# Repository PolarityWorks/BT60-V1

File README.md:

# BT60 V1

This is the repository of the design files for the Polarity Works [BT60 V1](https://www.polarityworks.com/bt60) containing both schematic and layout files for the soldered and hotswap variants

The files were created in Autodesk Eagle V9.6.2, in the event you do not have a licence for this software we also provide the schematics in PDF format

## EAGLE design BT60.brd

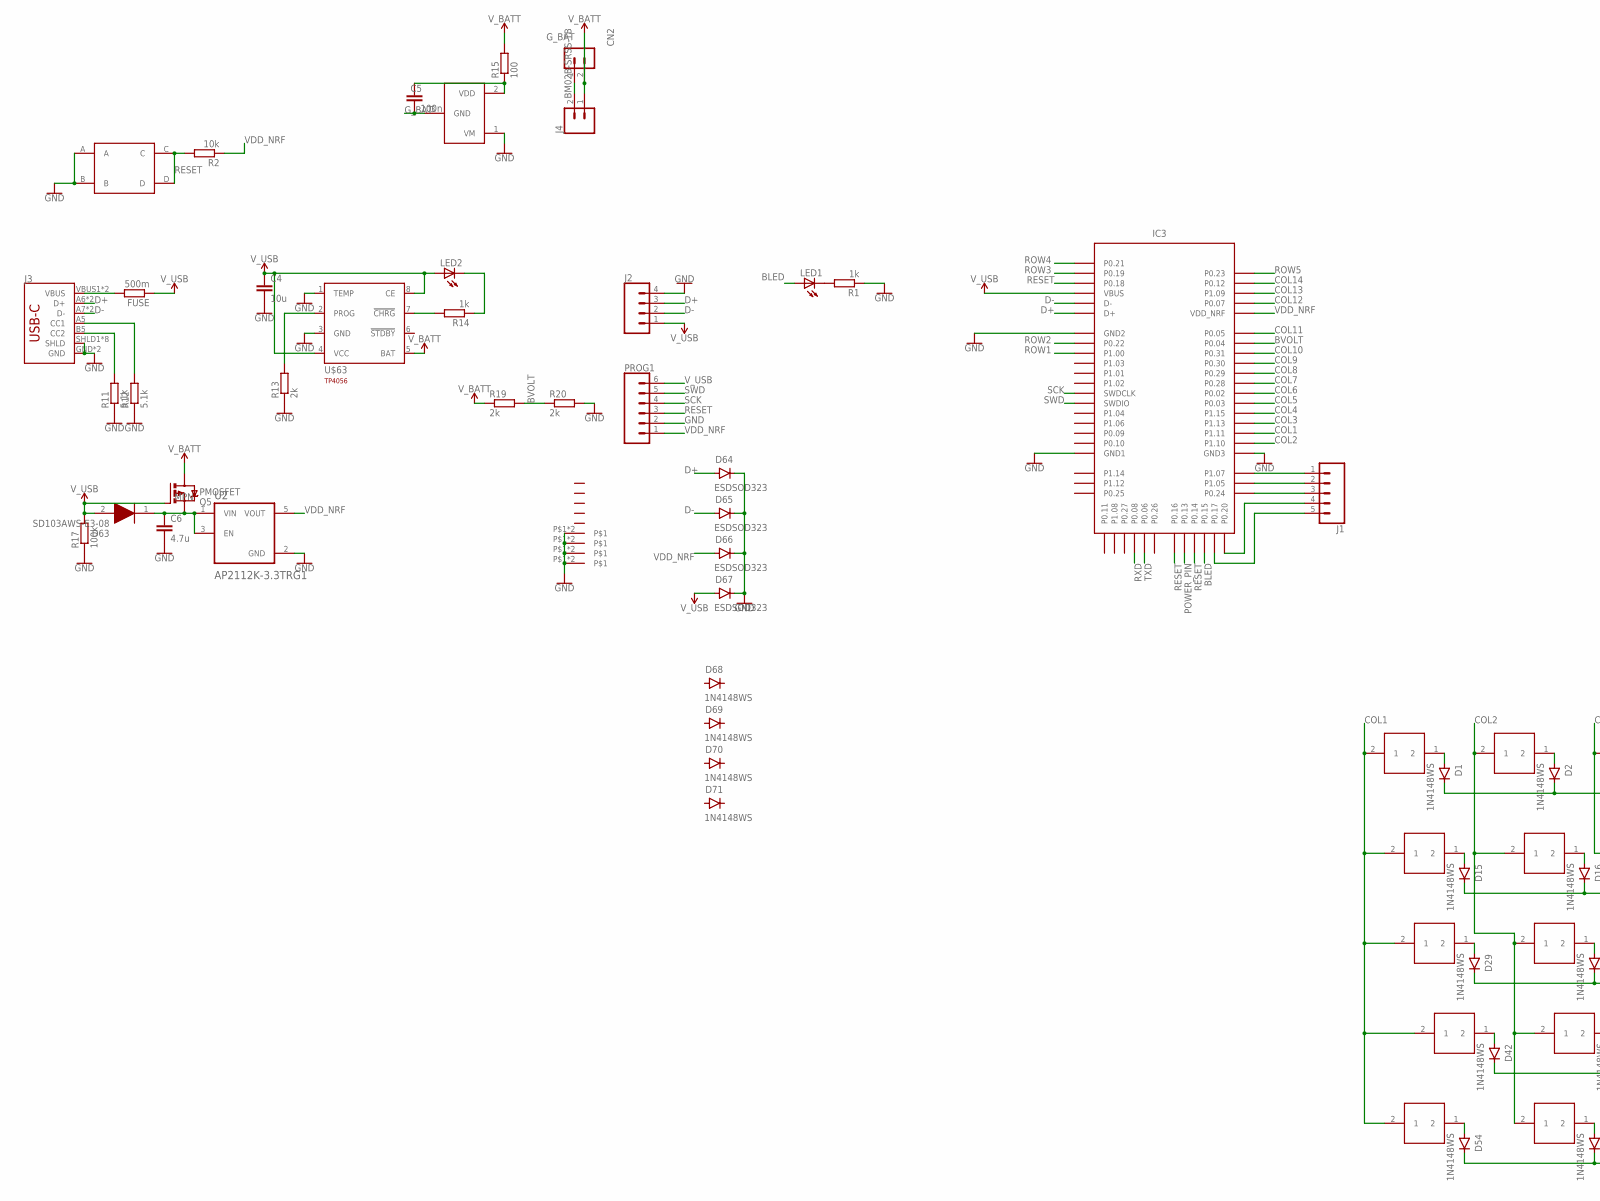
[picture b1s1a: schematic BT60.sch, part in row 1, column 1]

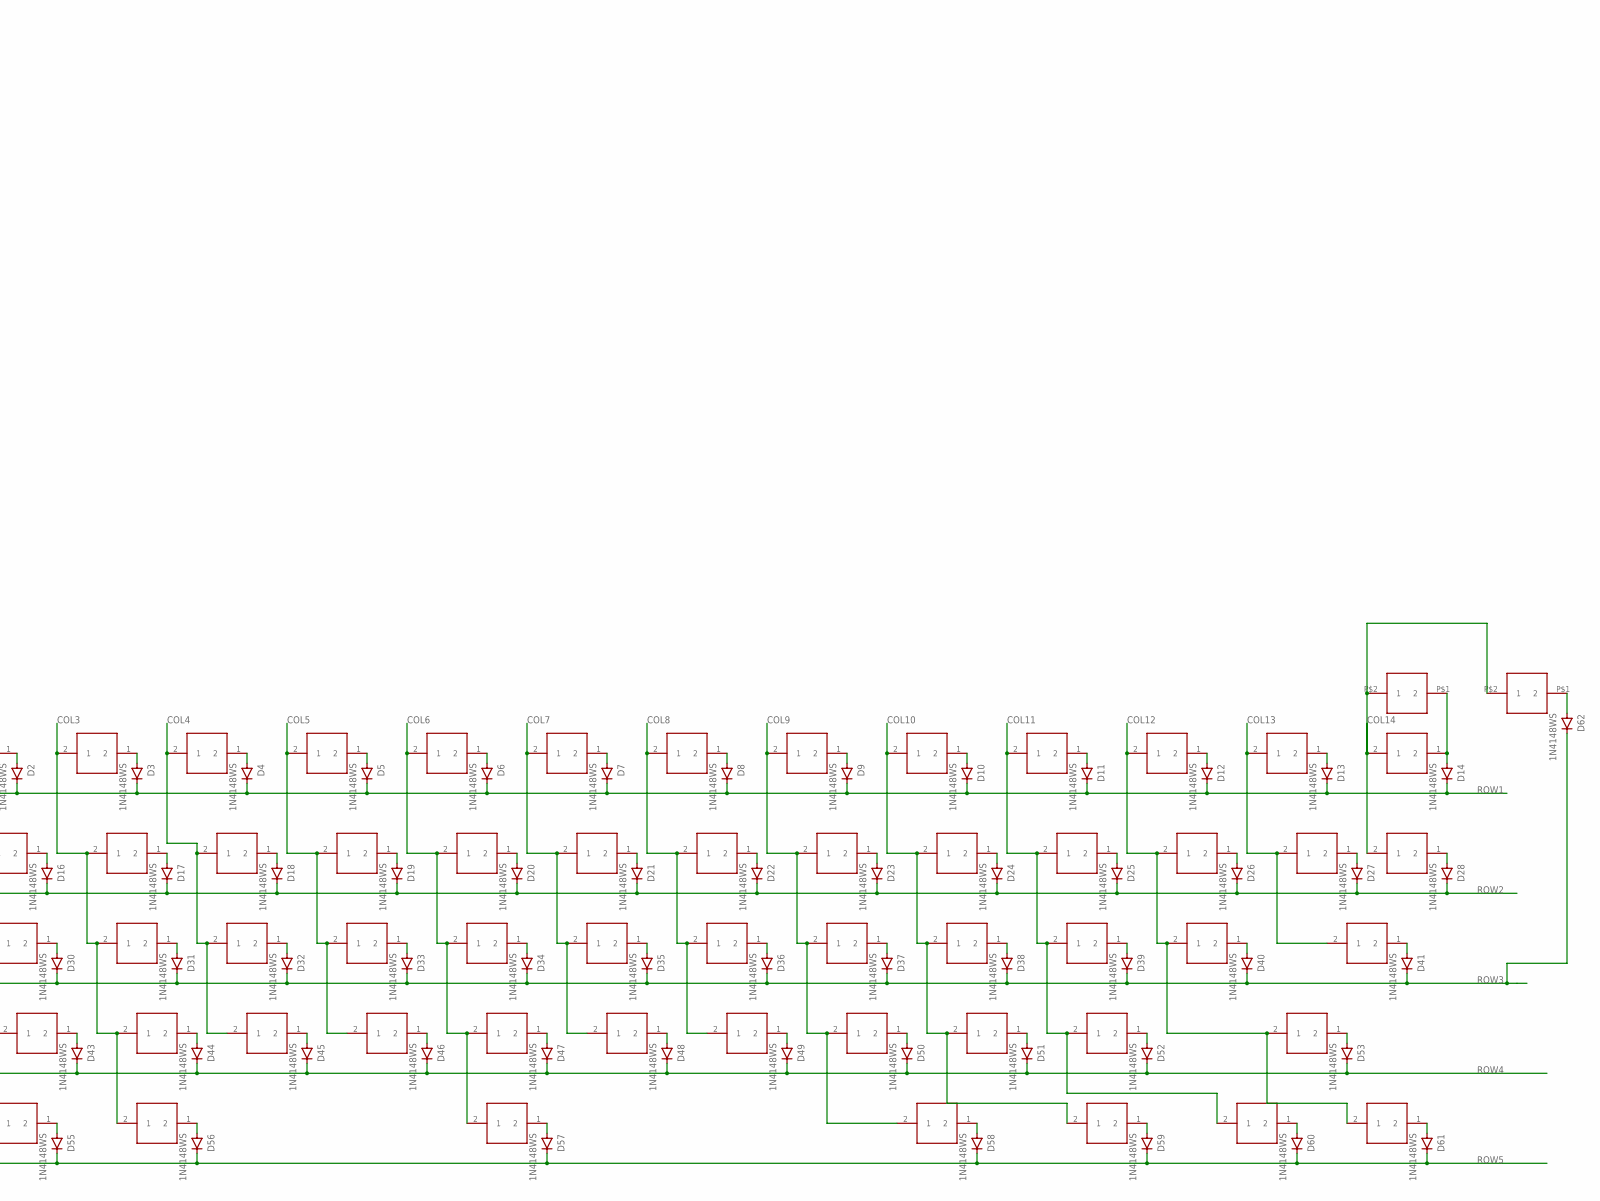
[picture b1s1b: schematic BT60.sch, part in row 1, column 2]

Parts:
C4: 10u; C0603
C5: 100n; C0603
C6: 4.7u; C0603
CN2: BM02B-SRSS-TB
D1, D2, D3, D4, D5, D6, D7, D8, D9, D10, D11, D12, D13, D14, D15, D16, D17, D18, D19, D20, D21, D22, D23, D24, D25, D26, D27, D28, D29, D30, D31, D32, D33, D34, D35, D36, D37, D38, D39, D40, D41, D42, D43, D44, D45, D46, D47, D48, D49, D50, D51, D52, D53, D54, D55, D56, D57, D58, D59, D60, D61, D62, D68, D69, D70, D71: 1N4148WS; SOD-323
D63: SD103AWS-E3-08; SOD2713X115N
D64, D65, D66, D67: ESDSOD323; SOD-323
FUSE: 500m; R0603
IC1: XB3303ASOT23; SOT23-3
IC3: HOLYIOT_18010; PCBCOMPONENT_1
J1: CONN_051.27MM; 1X05_1.27MM
J2: CONN_041X04_NO_SILK; 1X04_NO_SILK
J3: SPARKFUN-CONNECTORS_USB_C16PIN; SPARKFUN-CONNECTORS_USB-C-16P
J4: CONN_02; 1X02
LED1, LED2: LEDCHIPLED_0805; CHIPLED_0805
PROG1: CONN_06NO_SILK_FEMALE_PTH; 1X06_NO_SILK
Q5: PMOSFET; SOT23; MPN SL2301S
R1, R14: 1k; R0603
R2: 10k; R0603
R11, R12: 5.1k; R0603
R13, R19, R20: 2k; R0603
R15: 100; R0603
R17: 100k; R0603
U2: AP2112K-3.3TRG1; SOT95P285X140-5N
U$1, U$2, U$3, U$4, U$5, U$6, U$7, U$8, U$9, U$10, U$11, U$12, U$13, U$15, U$16, U$17, U$18, U$19, U$20, U$21, U$22, U$23, U$24, U$25, U$26, U$27, U$29, U$30, U$31, U$32, U$33, U$34, U$36, U$37, U$38, U$39, U$40, U$41, U$42, U$43, U$44, U$45, U$46, U$47, U$48, U$49, U$50, U$51, U$52, U$53, U$54, U$55, U$56, U$57, U$58, U$59, U$60, U$61: CHERRY
U$14, U$28, U$35: CHERRY_CORNER_OFFED
U$62: SMD-BUTTON
U$63: TP4056SOI8; SOIC8
U$64, U$65, U$67: 2.5MM_ELONGATED
U$66: 2.5MM_HOLE
U$68, U$69, U$70, U$71: STAB-2U
U$72: STAB-6U; STAB-6.25U
U$73, U$74: CHERRY-SOLDER

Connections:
BLED: IC3.P0.15, LED1.A
BVOLT: IC3.P0.04, R19.2, R20.1
COL1: IC3.P1.11, U$1.2 (1), U$15.2 (1), U$29.2 (1), U$42.2 (1), U$54.2 (1)
COL2: IC3.P1.10, U$2.2 (1), U$16.2 (1), U$30.2 (1), U$43.2 (1), U$55.2 (1)
COL3: IC3.P1.13, U$3.2 (1), U$17.2 (1), U$31.2 (1), U$44.2 (1), U$56.2 (1)
COL4: IC3.P1.15, U$4.2 (1), U$18.2 (1), U$32.2 (1), U$45.2 (1)
COL5: IC3.P0.03, U$5.2 (1), U$19.2 (1), U$33.2 (1), U$46.2 (1)
COL6: IC3.P0.02, U$6.2 (1), U$20.2 (1), U$34.2 (1), U$47.2 (1), U$57.2 (1)
COL7: IC3.P0.28, U$7.2 (1), U$21.2 (1), U$35.2 (1), U$48.2 (1)
COL8: IC3.P0.29, U$8.2 (1), U$22.2 (1), U$36.2 (1), U$49.2 (1)
COL9: IC3.P0.30, U$9.2 (1), U$23.2 (1), U$37.2 (1), U$50.2 (1), U$58.2 (1)
COL10: IC3.P0.31, U$10.2 (1), U$24.2 (1), U$38.2 (1), U$51.2 (1), U$59.2 (1)
COL11: IC3.P0.05, U$11.2 (1), U$25.2 (1), U$39.2 (1), U$52.2 (1), U$60.2 (1)
COL12: IC3.P0.07, U$12.2 (1), U$26.2 (1), U$40.2 (1), U$53.2 (1), U$61.2 (1)
COL13: IC3.P1.09, U$13.2 (1), U$27.2 (1), U$41.2 (1)
COL14: IC3.P0.12, U$14.2 (1), U$28.2 (1), U$73.P$2 (1), U$74.P$2 (1)
D+: D64.A, IC3.D+, J2.3, J3.A6 (D+), J3.B6 (D+)
D-: D65.A, IC3.D-, J2.2, J3.A7 (D-), J3.B7 (D-)
GND: C4.2, C6.2, D64.C, D65.C, D66.C, D67.C, IC1.1 (VM), IC3.GND (GND1), IC3.GND1 (GND2), IC3.GND2 (GND3), J2.4, J3.GND, J3.GND2 (GND), J3.SHLD1 (SHLD), J3.SHLD2 (SHLD), J3.SHLD3 (SHLD), J3.SHLD4 (SHLD), J3.SHLD5 (SHLD), J3.SHLD6 (SHLD), J3.SHLD7 (SHLD), J3.SHLD8 (SHLD), PROG1.2, R1.1, R11.1, R12.1, R13.1, R17.1, R20.2, U2.2 (GND), U$62.A, U$62.B, U$63.1 (TEMP), U$63.3 (GND), U$64.P$1, U$64.P$2, U$65.P$1, U$65.P$2, U$66.P$1, U$66.P$2, U$67.P$1, U$67.P$2
G_BAT: C5.2, CN2.1, IC1.3 (GND), J4.2
unnamed: D1.A, U$1.1 (2)
unnamed: LED1.C, R1.2
unnamed: D14.A, U$14.1 (2), U$73.P$1 (2)
unnamed: D13.A, U$13.1 (2)
unnamed: D12.A, U$12.1 (2)
unnamed: D11.A, U$11.1 (2)
unnamed: D10.A, U$10.1 (2)
unnamed: D9.A, U$9.1 (2)
unnamed: D8.A, U$8.1 (2)
unnamed: D7.A, U$7.1 (2)
unnamed: D6.A, U$6.1 (2)
unnamed: D5.A, U$5.1 (2)
unnamed: D4.A, U$4.1 (2)
unnamed: D3.A, U$3.1 (2)
unnamed: D2.A, U$2.1 (2)
unnamed: D15.A, U$15.1 (2)
unnamed: IC3.P1.07, J1.1
unnamed: D28.A, U$28.1 (2)
unnamed: D27.A, U$27.1 (2)
unnamed: D26.A, U$26.1 (2)
unnamed: D25.A, U$25.1 (2)
unnamed: D24.A, U$24.1 (2)
unnamed: D23.A, U$23.1 (2)
unnamed: D22.A, U$22.1 (2)
unnamed: D21.A, U$21.1 (2)
unnamed: D20.A, U$20.1 (2)
unnamed: D19.A, U$19.1 (2)
unnamed: D18.A, U$18.1 (2)
unnamed: D17.A, U$17.1 (2)
unnamed: D16.A, U$16.1 (2)
unnamed: D29.A, U$29.1 (2)
unnamed: IC3.P1.05, J1.2
unnamed: D41.A, U$41.1 (2)
unnamed: D40.A, U$40.1 (2)
unnamed: D39.A, U$39.1 (2)
unnamed: D38.A, U$38.1 (2)
unnamed: D37.A, U$37.1 (2)
unnamed: D36.A, U$36.1 (2)
unnamed: D35.A, U$35.1 (2)
unnamed: D34.A, U$34.1 (2)
unnamed: D33.A, U$33.1 (2)
unnamed: D32.A, U$32.1 (2)
unnamed: D31.A, U$31.1 (2)
unnamed: D30.A, U$30.1 (2)
unnamed: D42.A, U$42.1 (2)
unnamed: IC3.P0.24, J1.3
unnamed: D53.A, U$53.1 (2)
unnamed: D52.A, U$52.1 (2)
unnamed: D51.A, U$51.1 (2)
unnamed: D50.A, U$50.1 (2)
unnamed: D49.A, U$49.1 (2)
unnamed: D48.A, U$48.1 (2)
unnamed: D47.A, U$47.1 (2)
unnamed: D46.A, U$46.1 (2)
unnamed: D45.A, U$45.1 (2)
unnamed: D44.A, U$44.1 (2)
unnamed: D43.A, U$43.1 (2)
unnamed: D54.A, U$54.1 (2)
unnamed: IC3.P0.20, J1.4
unnamed: D61.A, U$61.1 (2)
unnamed: D60.A, U$60.1 (2)
unnamed: D59.A, U$59.1 (2)
unnamed: D58.A, U$58.1 (2)
unnamed: D57.A, U$57.1 (2)
unnamed: D56.A, U$56.1 (2)
unnamed: D55.A, U$55.1 (2)
unnamed: IC3.P0.17, J1.5
unnamed: D62.A, U$74.P$1 (2)
unnamed: C5.1, IC1.2 (VDD), R15.1
unnamed: FUSE.2, J3.VBUS1 (VBUS), J3.VBUS2 (VBUS)
unnamed: J3.B5 (CC2), R11.2
unnamed: J3.A5 (CC1), R12.2
unnamed: R13.2, U$63.2 (PROG)
unnamed: LED2.C, R14.1
unnamed: R14.2, U$63.7 (!CHRG)
unnamed: C6.1, D63.1 (K), Q5.2 (S), U2.1 (VIN), U2.3 (EN)
POWER_PIN: IC3.P0.13
RESET: IC3.P0.14, IC3.P0.16, IC3.P0.18, PROG1.3, R2.2, U$62.C, U$62.D
ROW1: D1.C, D2.C, D3.C, D4.C, D5.C, D6.C, D7.C, D8.C, D9.C, D10.C, D11.C, D12.C, D13.C, D14.C, IC3.P1.00
ROW2: D15.C, D16.C, D17.C, D18.C, D19.C, D20.C, D21.C, D22.C, D23.C, D24.C, D25.C, D26.C, D27.C, D28.C, IC3.P0.22
ROW3: D29.C, D30.C, D31.C, D32.C, D33.C, D34.C, D35.C, D36.C, D37.C, D38.C, D39.C, D40.C, D41.C, D62.C, IC3.P0.19
ROW4: D42.C, D43.C, D44.C, D45.C, D46.C, D47.C, D48.C, D49.C, D50.C, D51.C, D52.C, D53.C, IC3.P0.21
ROW5: D54.C, D55.C, D56.C, D57.C, D58.C, D59.C, D60.C, D61.C, IC3.P0.23
RXD: IC3.P0.08
SCK: IC3.SWDCLK, PROG1.4
SWD: IC3.SWDIO, PROG1.5
TXD: IC3.P0.06
VDD_NRF: D66.A, IC3.VDD_NRF, PROG1.1, R2.1, U2.5 (VOUT)
V_BATT: CN2.2, J4.1, Q5.3 (D), R15.2, R19.1, U$63.5 (BAT)
V_USB: C4.1, D63.2 (A), D67.A, FUSE.1, IC3.VBUS, J2.1, LED2.A, PROG1.6, Q5.1 (G), R17.2, U$63.4 (VCC), U$63.8 (CE)

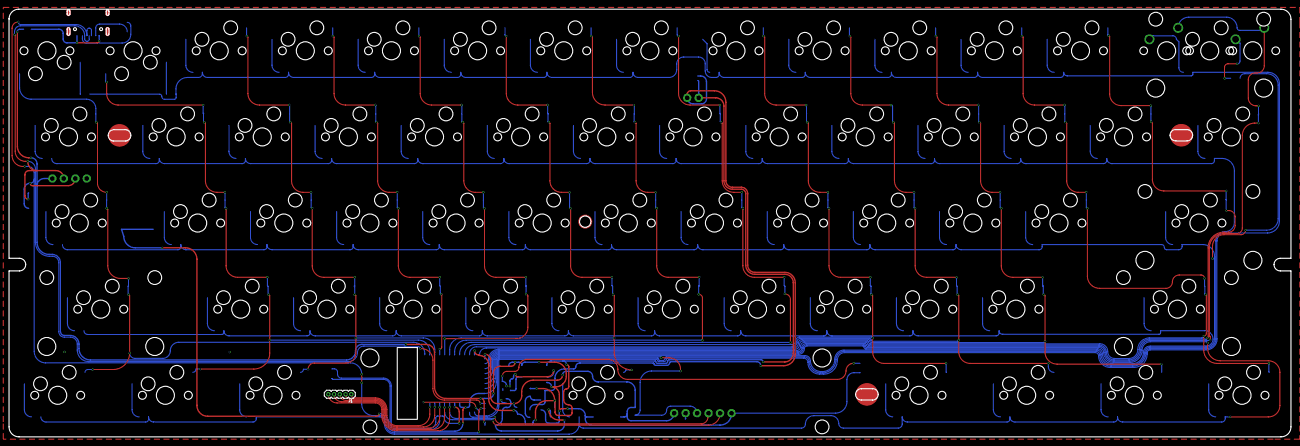
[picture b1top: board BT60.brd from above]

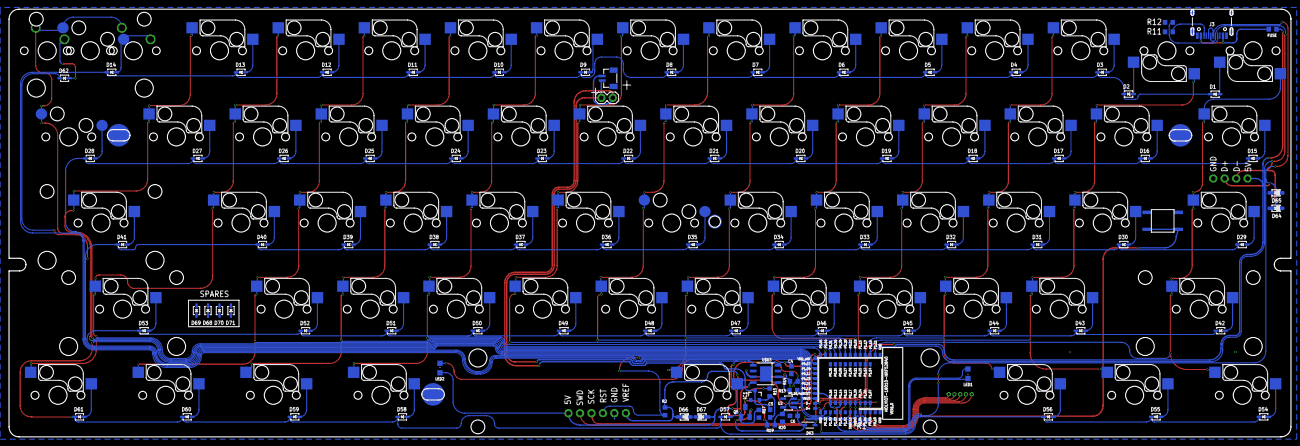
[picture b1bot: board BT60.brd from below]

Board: 2 copper layers, 283.5 x 94.6 mm, 171 parts (96 on the bottom side), 107 nets.

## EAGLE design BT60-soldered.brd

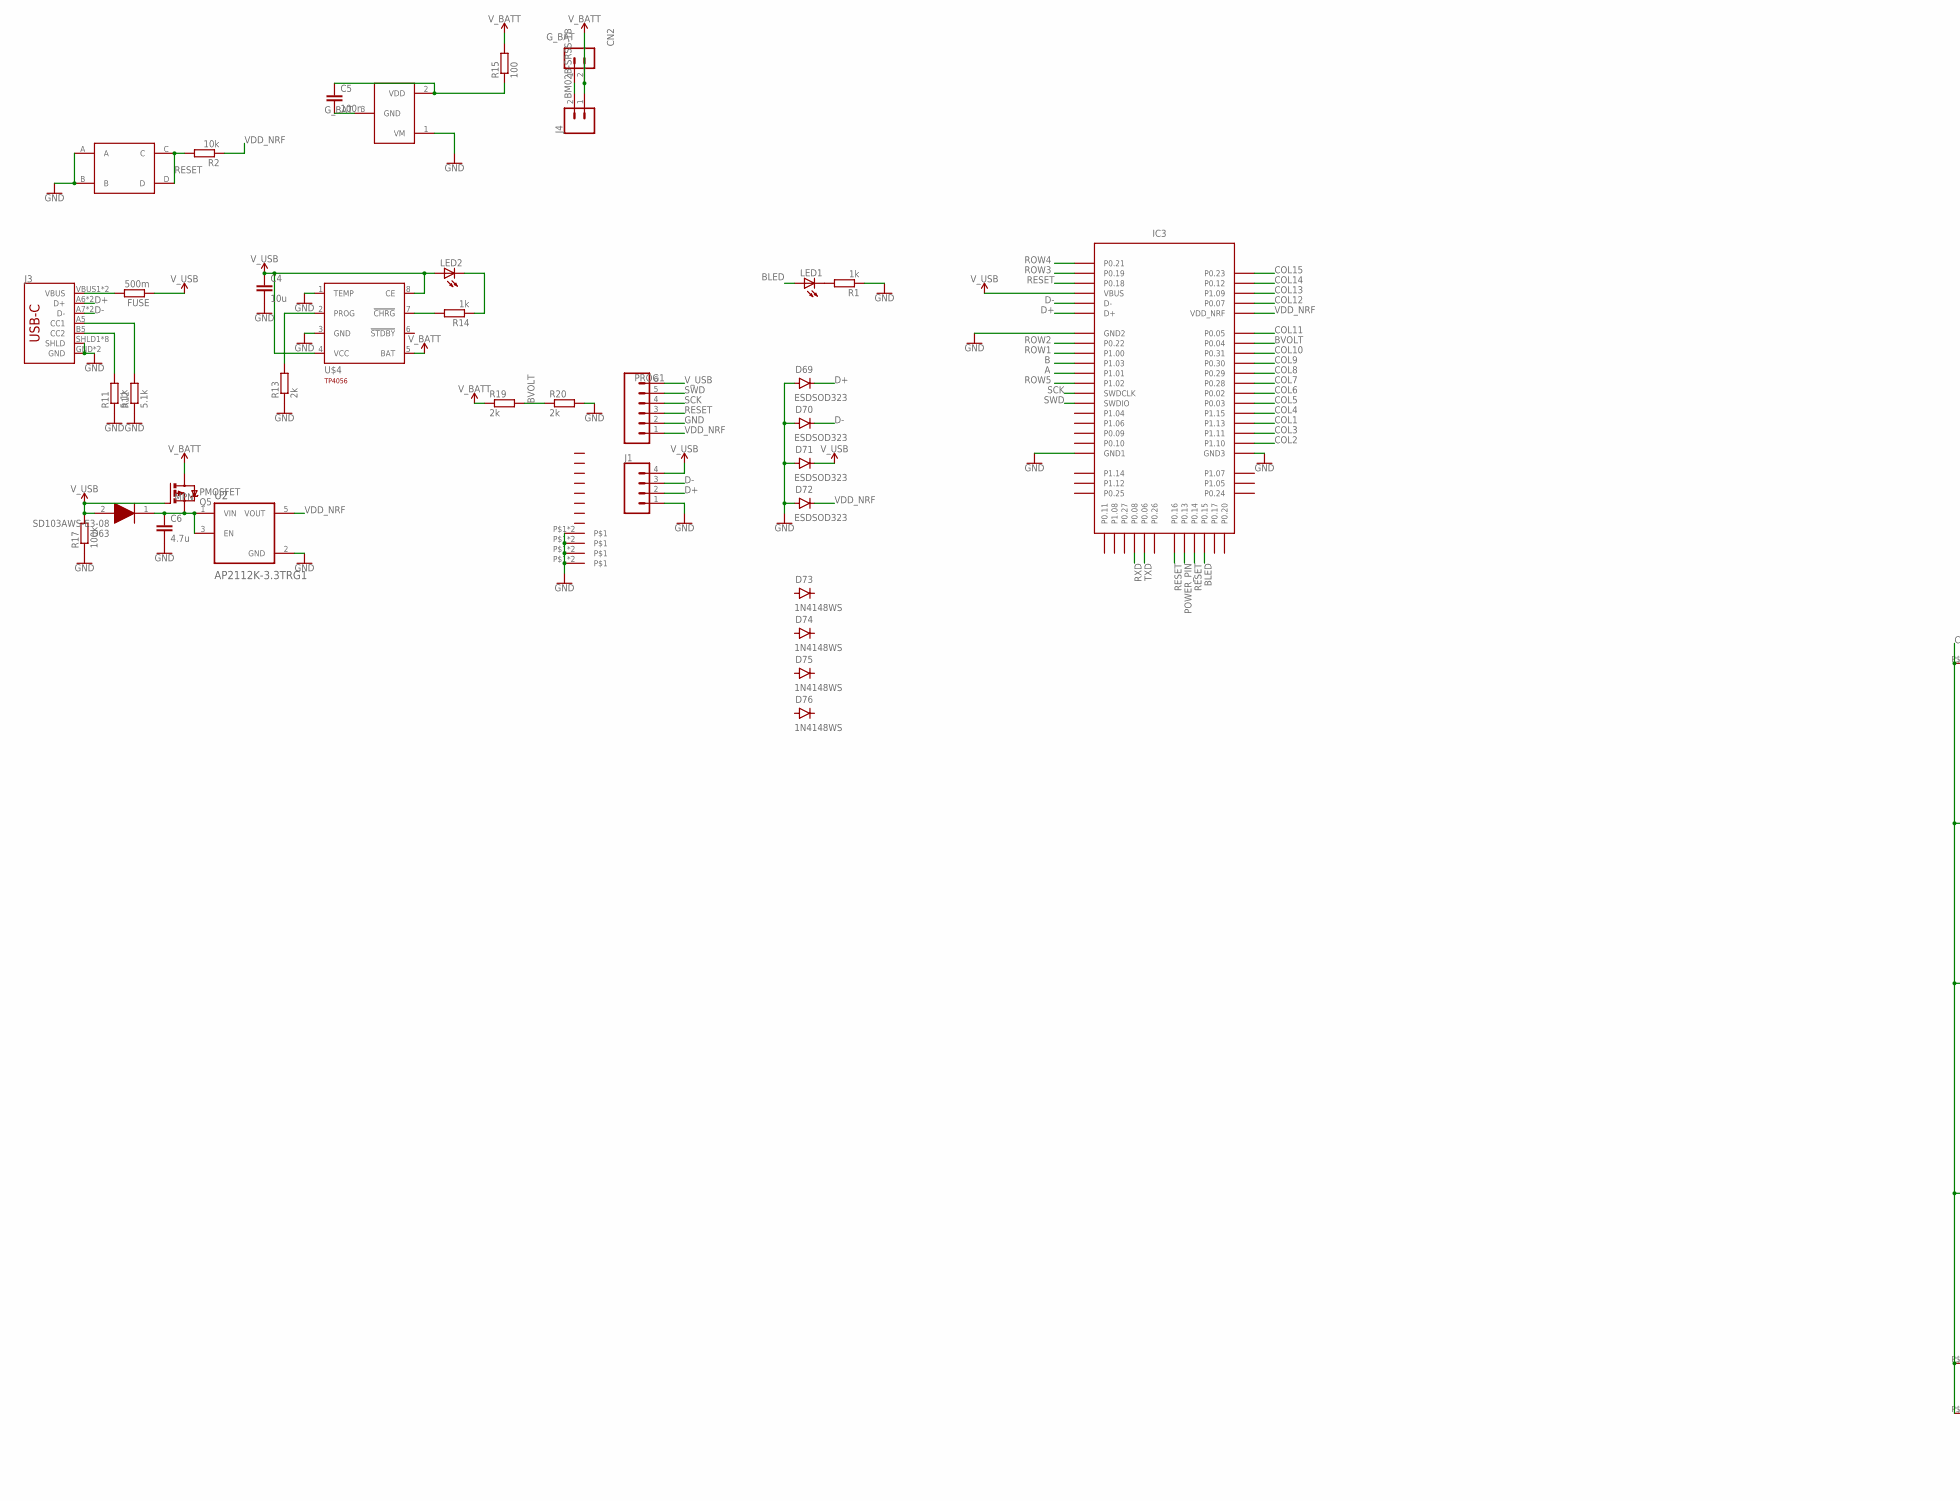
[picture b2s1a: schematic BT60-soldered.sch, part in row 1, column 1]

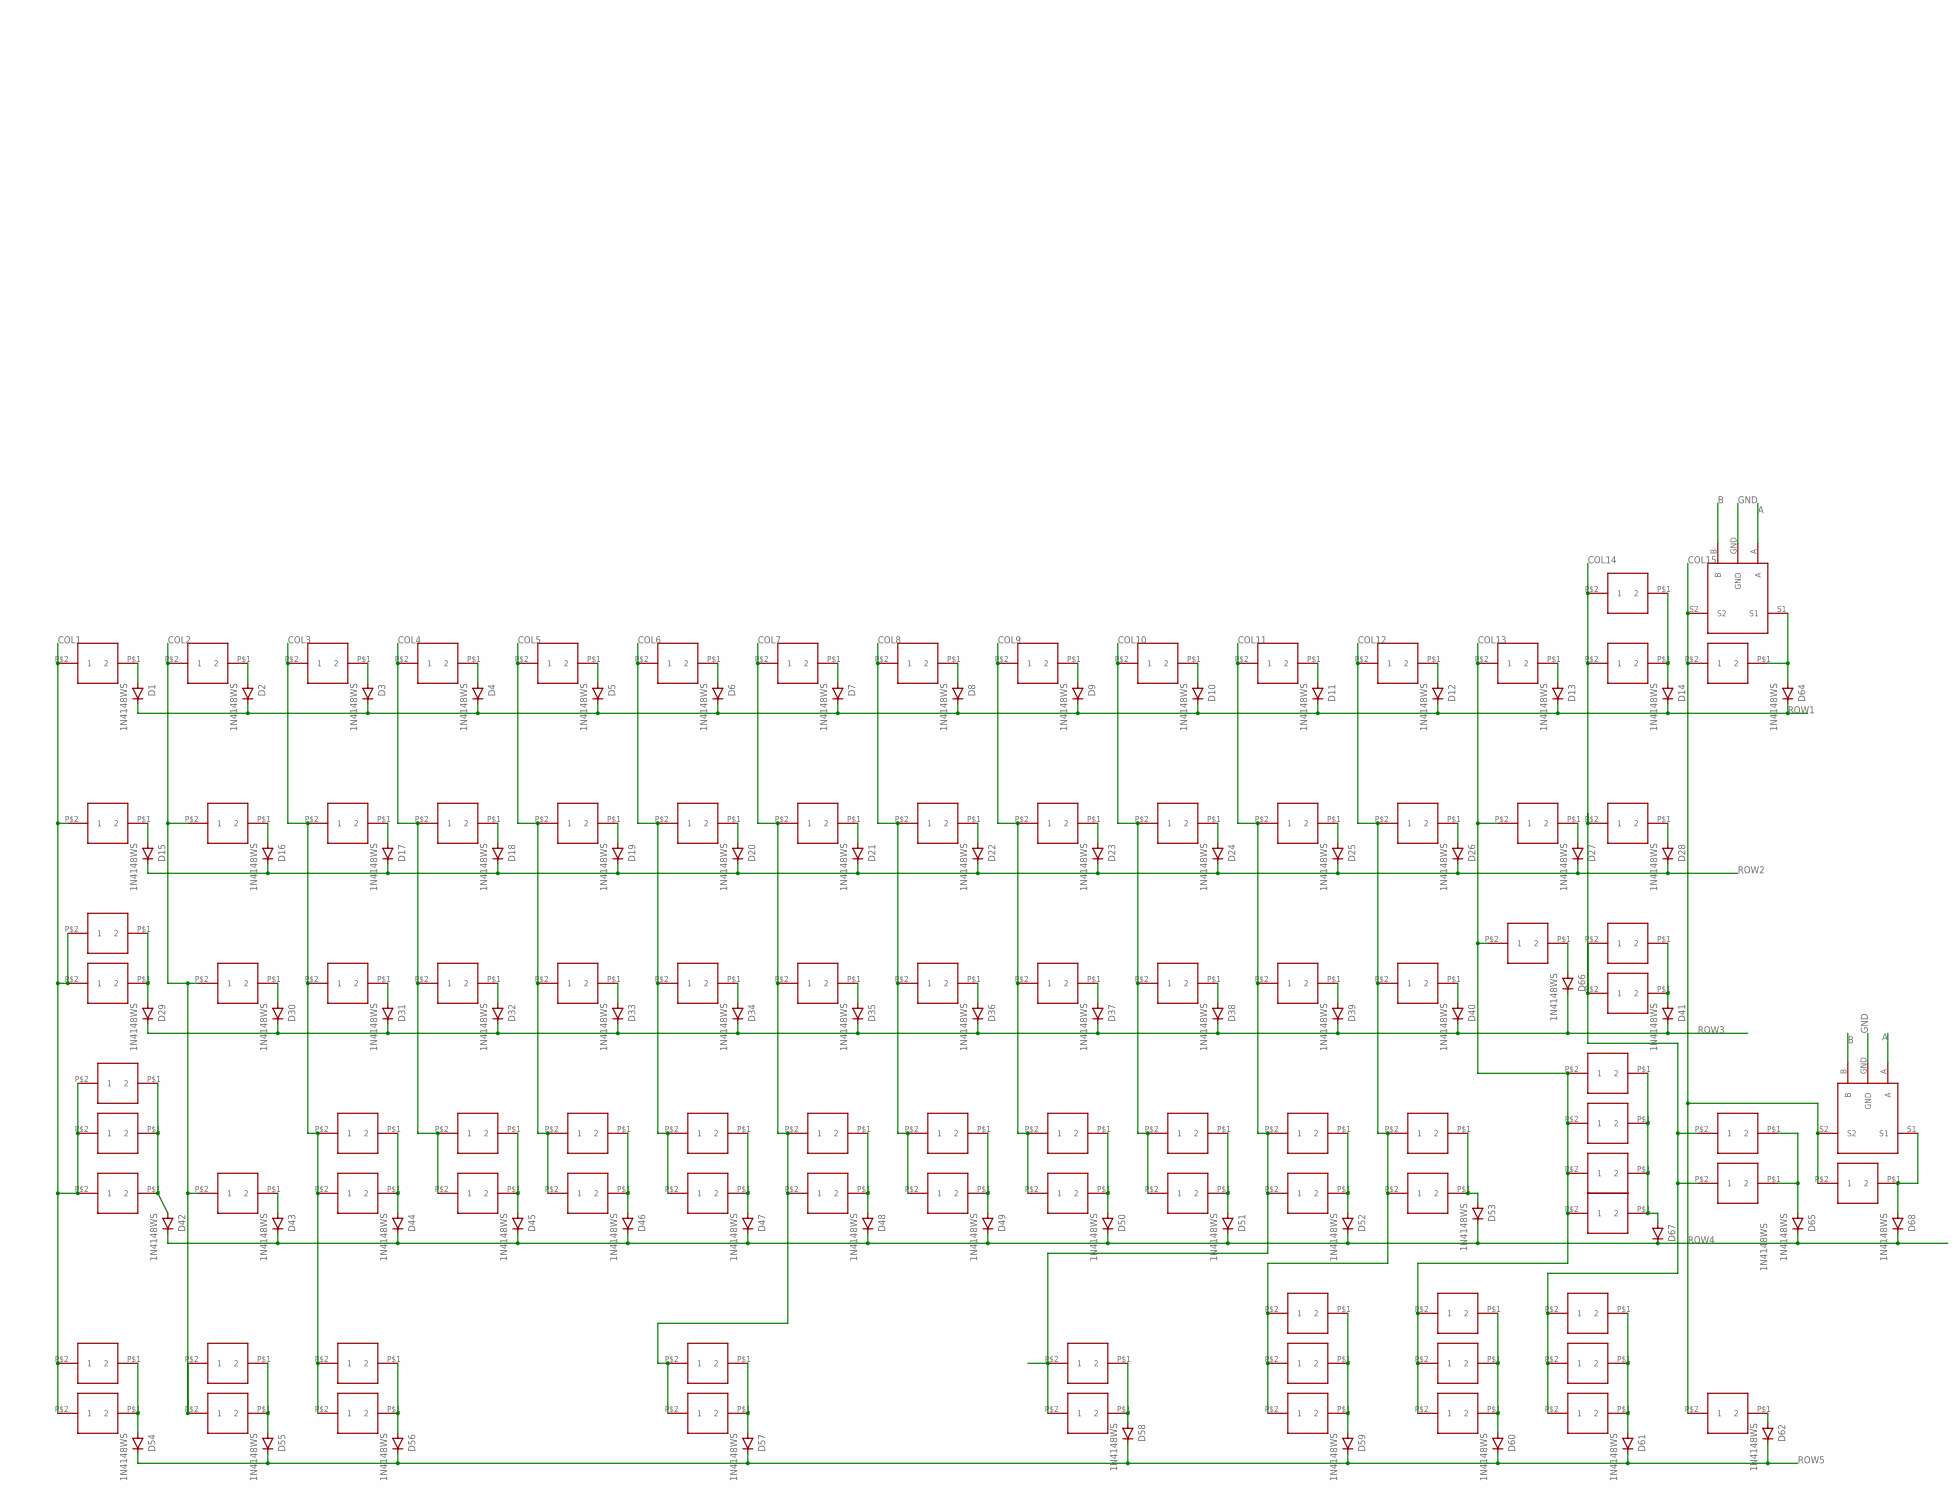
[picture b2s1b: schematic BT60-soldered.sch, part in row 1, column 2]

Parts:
0, 1, 1U_1, 1U_2, 1U_3, 1U_4, 1U_5, 2, 3, 4, 5, 6, 7, 8, 9, ., ._1: CHERRY-SOLDER
#_ISO: CHERRY-SOLDER
': CHERRY-SOLDER
,: CHERRY-SOLDER
,_1: CHERRY-SOLDER
-: CHERRY-SOLDER
/: CHERRY-SOLDER
/_1: CHERRY-SOLDER
=: CHERRY-SOLDER
A: CHERRY-SOLDER
B: CHERRY-SOLDER
BS: CHERRY-SOLDER
B_1: CHERRY-SOLDER
C: CHERRY-SOLDER
C4: 10u; C0603
C5: 100n; C0603
C6: 4.7u; C0603
CAPS: CHERRY-SOLDER
CAPS_STEP: CHERRY-SOLDER
CN2: BM02B-SRSS-TB
COLON: CHERRY-SOLDER
C_1: CHERRY-SOLDER
D: CHERRY-SOLDER
D1, D2, D3, D4, D5, D6, D7, D8, D9, D10, D11, D12, D13, D14, D15, D16, D17, D18, D19, D20, D21, D22, D23, D24, D25, D26, D27, D28, D29, D30, D31, D32, D33, D34, D35, D36, D37, D38, D39, D40, D41, D42, D43, D44, D45, D46, D47, D48, D49, D50, D51, D52, D53, D54, D55, D56, D57, D58, D59, D60, D61, D62, D64, D65, D66, D67, D68, D73, D74, D75, D76: 1N4148WS; SOD-323
D63: SD103AWS-E3-08; SOD2713X115N
D69, D70, D71, D72: ESDSOD323; SOD-323
E: CHERRY-SOLDER
ENTER: CHERRY-SOLDER
ESC: CHERRY-SOLDER
EXTRA_1U_LEFT: CHERRY-SOLDER
F: CHERRY-SOLDER
FN: CHERRY-SOLDER
FUSE: 500m; R0603
G: CHERRY-SOLDER
H: CHERRY-SOLDER
I: CHERRY-SOLDER
IC3: HOLYIOT_18010; PCBCOMPONENT_1
ISO_#: CHERRY-SOLDER
ISO_ENTER: CHERRY-SOLDER
J: CHERRY-SOLDER
J1: CONN_041X04_NO_SILK; 1X04_NO_SILK
J3: SPARKFUN-CONNECTORS_USB_C16PIN; SPARKFUN-CONNECTORS_USB-C-16P
J4: CONN_02; 1X02
K: CHERRY-SOLDER
L: CHERRY-SOLDER
LALT: CHERRY-SOLDER
LALT_1.5U: CHERRY-SOLDER
LCTRL: CHERRY-SOLDER
LCTRL_1.5U: CHERRY-SOLDER
LED1, LED2: LEDCHIPLED_0805; CHIPLED_0805
LWIN: CHERRY-SOLDER
LWIN_1U: CHERRY-SOLDER
L_1.25U_SHIFT, L_2U_SHIFT: CHERRY-SOLDER
L_SHIFT: CHERRY-SOLDER
M: CHERRY-SOLDER
MENU: CHERRY-SOLDER
MENU_1U: CHERRY-SOLDER
M_1: CHERRY-SOLDER
N: CHERRY-SOLDER
N_1: CHERRY-SOLDER
O: CHERRY-SOLDER
P: CHERRY-SOLDER
PROG1: CONN_06NO_SILK_FEMALE_PTH; 1X06_NO_SILK
Q: CHERRY-SOLDER
Q5: PMOSFET; SOT23; MPN SL2301S
R: CHERRY-SOLDER
R1, R14: 1k; R0603
R2: 10k; R0603
R11, R12: 5.1k; R0603
R13, R19, R20: 2k; R0603
R15: 100; R0603
R17: 100k; R0603
RALT: CHERRY-SOLDER
RCTRL: CHERRY-SOLDER
R_ALT_1.5: CHERRY-SOLDER
R_CTRL_1.5U: CHERRY-SOLDER
R_SHIFT: CHERRY-SOLDER
R_SHIFT_1.75U_LEFT, R_SHIFT_1.75U_RIGHT: CHERRY-SOLDER
S: CHERRY-SOLDER
SPACE_6.25U, SPACE_7U: CHERRY-SOLDER
SPLIT_BS_1, SPLIT_BS_2: CHERRY-SOLDER
T: CHERRY-SOLDER
TAB: CHERRY-SOLDER
U: CHERRY-SOLDER
U2: AP2112K-3.3TRG1; SOT95P285X140-5N
U$1, U$2: CHERRY-ENCODER
U$3: XB3303ASOT23; SOT23-3
U$4: TP4056SOI8; SOIC8
U$62: SMD-BUTTON
U$64, U$65, U$66, U$67: 2.5MM_ELONGATED
U$68, U$69, U$70, U$71, U$83, U$108: STAB-2U
U$72: STAB-6U; STAB-6.25U
U$91: STAB-7U
UP: CHERRY-SOLDER
V: CHERRY-SOLDER
V_1: CHERRY-SOLDER
W: CHERRY-SOLDER
X, X5U_1, X5U_2: CHERRY-SOLDER
X_1: CHERRY-SOLDER
Y: CHERRY-SOLDER
Z: CHERRY-SOLDER
Z_1: CHERRY-SOLDER
[: CHERRY-SOLDER
\: CHERRY-SOLDER
]: CHERRY-SOLDER

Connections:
A: IC3.P1.01, U$1.A, U$2.A
B: IC3.P1.03, U$1.B, U$2.B
BLED: IC3.P0.15, LED1.A
BVOLT: IC3.P0.04, R19.2, R20.1
COL1: CAPS.P$2 (1), CAPS_STEP.P$2 (1), ESC.P$2 (1), IC3.P1.13, LCTRL.P$2 (1), LCTRL_1.5U.P$2 (1), L_1.25U_SHIFT.P$2 (1), L_2U_SHIFT.P$2 (1), L_SHIFT.P$2 (1), TAB.P$2 (1)
COL2: 1.P$2 (1), #_ISO.P$2 (1), A.P$2 (1), IC3.P1.10, LWIN.P$2 (1), LWIN_1U.P$2 (1), Q.P$2 (1)
COL3: 2.P$2 (1), IC3.P1.11, LALT.P$2 (1), LALT_1.5U.P$2 (1), S.P$2 (1), W.P$2 (1), Z.P$2 (1), Z_1.P$2 (1)
COL4: 3.P$2 (1), D.P$2 (1), E.P$2 (1), IC3.P1.15, X.P$2 (1), X_1.P$2 (1)
COL5: 4.P$2 (1), C.P$2 (1), C_1.P$2 (1), F.P$2 (1), IC3.P0.03, R.P$2 (1)
COL6: 5.P$2 (1), G.P$2 (1), IC3.P0.02, T.P$2 (1), V.P$2 (1), V_1.P$2 (1)
COL7: 6.P$2 (1), B.P$2 (1), B_1.P$2 (1), H.P$2 (1), IC3.P0.28, SPACE_6.25U.P$2 (1), SPACE_7U.P$2 (1), Y.P$2 (1)
COL8: 7.P$2 (1), IC3.P0.29, J.P$2 (1), N.P$2 (1), N_1.P$2 (1), U.P$2 (1)
COL9: 8.P$2 (1), I.P$2 (1), IC3.P0.30, K.P$2 (1), M.P$2 (1), M_1.P$2 (1)
COL10: 9.P$2 (1), ,.P$2 (1), ,_1.P$2 (1), IC3.P0.31, L.P$2 (1), O.P$2 (1)
COL11: 0.P$2 (1), 1U_1.P$2 (1), ..P$2 (1), ._1.P$2 (1), COLON.P$2 (1), IC3.P0.05, P.P$2 (1), RALT.P$2 (1)
COL12: 1U_2.P$2 (1), '.P$2 (1), -.P$2 (1), /.P$2 (1), /_1.P$2 (1), IC3.P0.07, MENU.P$2 (1), R_ALT_1.5.P$2 (1), [.P$2 (1)
COL13: 1U_3.P$2 (1), =.P$2 (1), EXTRA_1U_LEFT.P$2 (1), IC3.P1.09, ISO_#.P$2 (1), MENU_1U.P$2 (1), RCTRL.P$2 (1), R_SHIFT.P$2 (1), R_SHIFT_1.75U_LEFT.P$2 (1), UP.P$2 (1), ].P$2 (1)
COL14: 1U_4.P$2 (1), BS.P$2 (1), ENTER.P$2 (1), FN.P$2 (1), IC3.P0.12, ISO_ENTER.P$2 (1), R_CTRL_1.5U.P$2 (1), R_SHIFT_1.75U_RIGHT.P$2 (1), SPLIT_BS_1.P$2 (1), X5U_1.P$2 (1), \.P$2 (1)
COL15: 1U_5.P$2 (1), IC3.P0.23, SPLIT_BS_2.P$2 (1), U$1.S2, U$2.S2, X5U_2.P$2 (1)
D+: D69.C, IC3.D+, J1.2, J3.A6 (D+), J3.B6 (D+)
D-: D70.C, IC3.D-, J1.3, J3.A7 (D-), J3.B7 (D-)
GND: C4.2, C6.2, D69.A, D70.A, D71.A, D72.A, IC3.GND (GND1), IC3.GND1 (GND2), IC3.GND2 (GND3), J1.1, J3.GND, J3.GND2 (GND), J3.SHLD1 (SHLD), J3.SHLD2 (SHLD), J3.SHLD3 (SHLD), J3.SHLD4 (SHLD), J3.SHLD5 (SHLD), J3.SHLD6 (SHLD), J3.SHLD7 (SHLD), J3.SHLD8 (SHLD), PROG1.2, R1.1, R11.1, R12.1, R13.1, R17.1, R20.2, U2.2 (GND), U$1.GND, U$2.GND, U$3.1 (VM), U$4.1 (TEMP), U$4.3 (GND), U$62.A, U$62.B, U$64.P$1, U$64.P$2, U$65.P$1, U$65.P$2, U$66.P$1, U$66.P$2, U$67.P$1, U$67.P$2
G_BAT: C5.2, CN2.1, J4.2, U$3.3 (GND)
unnamed: D1.A, ESC.P$1 (2)
unnamed: LED1.C, R1.2
unnamed: 1U_5.P$1 (2), D62.A
unnamed: =.P$1 (2), D13.A
unnamed: -.P$1 (2), D12.A
unnamed: 0.P$1 (2), D11.A
unnamed: 9.P$1 (2), D10.A
unnamed: 8.P$1 (2), D9.A
unnamed: 7.P$1 (2), D8.A
unnamed: 6.P$1 (2), D7.A
unnamed: 5.P$1 (2), D6.A
unnamed: 4.P$1 (2), D5.A
unnamed: 3.P$1 (2), D4.A
unnamed: 2.P$1 (2), D3.A
unnamed: 1.P$1 (2), D2.A
unnamed: D15.A, TAB.P$1 (2)
unnamed: D45.A, X.P$1 (2), X_1.P$1 (2)
unnamed: D28.A, \.P$1 (2)
unnamed: D27.A, ].P$1 (2)
unnamed: D26.A, [.P$1 (2)
unnamed: D25.A, P.P$1 (2)
unnamed: D24.A, O.P$1 (2)
unnamed: D23.A, I.P$1 (2)
unnamed: D22.A, U.P$1 (2)
unnamed: D21.A, Y.P$1 (2)
unnamed: D20.A, T.P$1 (2)
unnamed: D19.A, R.P$1 (2)
unnamed: D18.A, E.P$1 (2)
unnamed: D17.A, W.P$1 (2)
unnamed: D16.A, Q.P$1 (2)
unnamed: D47.A, V.P$1 (2), V_1.P$1 (2)
unnamed: ,.P$1 (2), ,_1.P$1 (2), D51.A
unnamed: D41.A, ENTER.P$1 (2), ISO_ENTER.P$1 (2)
unnamed: '.P$1 (2), D40.A
unnamed: COLON.P$1 (2), D39.A
unnamed: D38.A, L.P$1 (2)
unnamed: D37.A, K.P$1 (2)
unnamed: D36.A, J.P$1 (2)
unnamed: D35.A, H.P$1 (2)
unnamed: D34.A, G.P$1 (2)
unnamed: D33.A, F.P$1 (2)
unnamed: D.P$1 (2), D32.A
unnamed: D31.A, S.P$1 (2)
unnamed: A.P$1 (2), D30.A
unnamed: D42.A, L_1.25U_SHIFT.P$1 (2), L_2U_SHIFT.P$1 (2), L_SHIFT.P$1 (2)
unnamed: ..P$1 (2), ._1.P$1 (2), D52.A
unnamed: D67.A, EXTRA_1U_LEFT.P$1 (2), R_SHIFT.P$1 (2), R_SHIFT_1.75U_LEFT.P$1 (2), UP.P$1 (2)
unnamed: D68.A, U$2.S1, X5U_2.P$1 (2)
unnamed: D64.A, SPLIT_BS_2.P$1 (2), U$1.S1
unnamed: C5.1, R15.1, U$3.2 (VDD)
unnamed: #_ISO.P$1 (2), D43.A
unnamed: D44.A, Z.P$1 (2), Z_1.P$1 (2)
unnamed: B.P$1 (2), B_1.P$1 (2), D48.A
unnamed: C.P$1 (2), C_1.P$1 (2), D46.A
unnamed: D49.A, N.P$1 (2), N_1.P$1 (2)
unnamed: D50.A, M.P$1 (2), M_1.P$1 (2)
unnamed: D54.A, LCTRL.P$1 (2), LCTRL_1.5U.P$1 (2)
unnamed: /.P$1 (2), /_1.P$1 (2), D53.A
unnamed: 1U_4.P$1 (2), D61.A, FN.P$1 (2), R_CTRL_1.5U.P$1 (2)
unnamed: 1U_3.P$1 (2), D60.A, MENU_1U.P$1 (2), RCTRL.P$1 (2)
unnamed: 1U_2.P$1 (2), D59.A, MENU.P$1 (2), R_ALT_1.5.P$1 (2)
unnamed: 1U_1.P$1 (2), D58.A, RALT.P$1 (2)
unnamed: D57.A, SPACE_6.25U.P$1 (2), SPACE_7U.P$1 (2)
unnamed: D56.A, LALT.P$1 (2), LALT_1.5U.P$1 (2)
unnamed: D55.A, LWIN.P$1 (2), LWIN_1U.P$1 (2)
unnamed: FUSE.2, J3.VBUS1 (VBUS), J3.VBUS2 (VBUS)
unnamed: BS.P$1 (2), D14.A, SPLIT_BS_1.P$1 (2)
unnamed: D66.A, ISO_#.P$1 (2)
unnamed: J3.B5 (CC2), R11.2
unnamed: J3.A5 (CC1), R12.2
unnamed: R13.2, U$4.2 (PROG)
unnamed: LED2.C, R14.1
unnamed: R14.2, U$4.7 (!CHRG)
unnamed: C6.1, D63.1 (K), Q5.2 (S), U2.1 (VIN), U2.3 (EN)
unnamed: CAPS.P$1 (2), CAPS_STEP.P$1 (2), D29.A
unnamed: D65.A, R_SHIFT_1.75U_RIGHT.P$1 (2), X5U_1.P$1 (2)
POWER_PIN: IC3.P0.13
RESET: IC3.P0.14, IC3.P0.16, IC3.P0.18, PROG1.3, R2.2, U$62.C, U$62.D
ROW1: D1.C, D2.C, D3.C, D4.C, D5.C, D6.C, D7.C, D8.C, D9.C, D10.C, D11.C, D12.C, D13.C, D14.C, D64.C, IC3.P1.00
ROW2: D15.C, D16.C, D17.C, D18.C, D19.C, D20.C, D21.C, D22.C, D23.C, D24.C, D25.C, D26.C, D27.C, D28.C, IC3.P0.22
ROW3: D29.C, D30.C, D31.C, D32.C, D33.C, D34.C, D35.C, D36.C, D37.C, D38.C, D39.C, D40.C, D41.C, D66.C, IC3.P0.19
ROW4: D42.C, D43.C, D44.C, D45.C, D46.C, D47.C, D48.C, D49.C, D50.C, D51.C, D52.C, D53.C, D65.C, D67.C, D68.C, IC3.P0.21
ROW5: D54.C, D55.C, D56.C, D57.C, D58.C, D59.C, D60.C, D61.C, D62.C, IC3.P1.02
RXD: IC3.P0.08
SCK: IC3.SWDCLK, PROG1.4
SWD: IC3.SWDIO, PROG1.5
TXD: IC3.P0.06
VDD_NRF: D72.C, IC3.VDD_NRF, PROG1.1, R2.1, U2.5 (VOUT)
V_BATT: CN2.2, J4.1, Q5.3 (D), R15.2, R19.1, U$4.5 (BAT)
V_USB: C4.1, D63.2 (A), D71.C, FUSE.1, IC3.VBUS, J1.4, LED2.A, PROG1.6, Q5.1 (G), R17.2, U$4.4 (VCC), U$4.8 (CE)

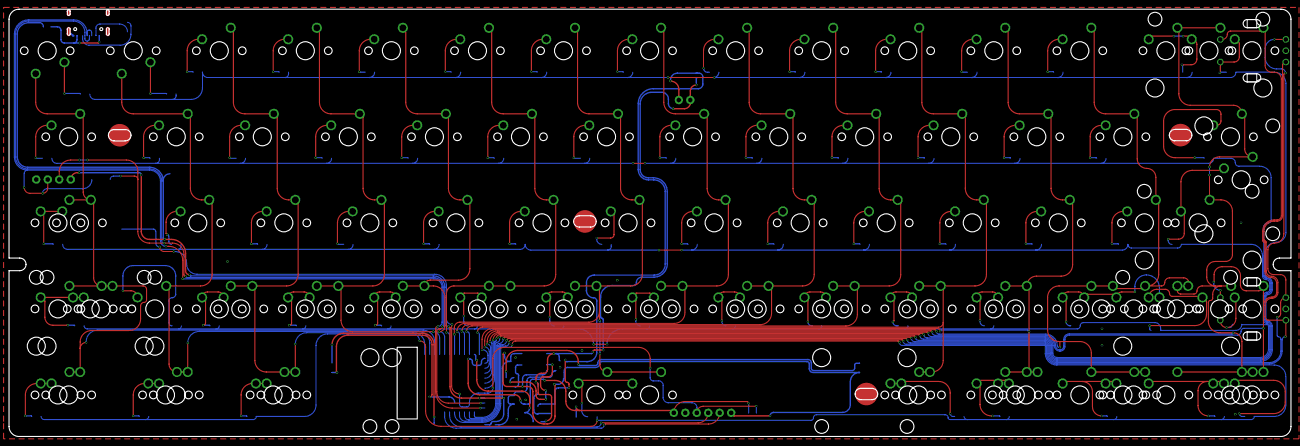
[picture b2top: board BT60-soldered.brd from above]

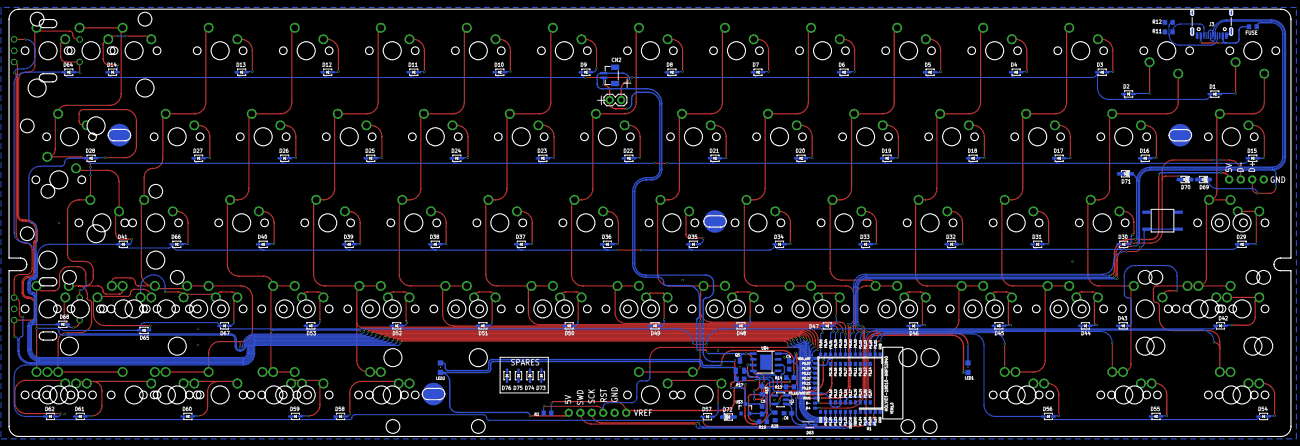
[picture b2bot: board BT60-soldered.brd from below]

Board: 2 copper layers, 283.8 x 94.6 mm, 214 parts (101 on the bottom side), 110 nets.

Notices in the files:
parts and their libraries:
User-Submitted: Licensing: Creative Commons ShareAlike 4.0 International - https://creativecommons.org/licenses/by-sa/4.0
